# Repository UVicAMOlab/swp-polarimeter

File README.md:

## Spinning Waveplate Polarimeter

*Using a rotating quarter waveplate, a photodiode, and a few Python scripts, we can produce real-time visualization of the polarization state of incident light. This fully integrated system is easily calibrated and an affordable alternative to other fussy optical technologies making it ideal for research laboratories and educational environments.*

# Real-time Detection of Polarization of Incident Light

Initially, we use the API provided by the DAQ hat to acquire a fixed number of samples for processing; typically, this is 1000 samples at 20 ksps when the waveplate is spinning between 4500 to 5500 RPM. The raw data input is then divided into segments. Each segment is numerically integrated to determine the Fourier coefficients, and furthermore, the Stokes parameters and polarization state. To minimize any statistical errors, the mean result over several segments is considered and the display is refreshed at a rate of 4 Hz.

The reconstruction of the Stokes vector is achieved by calculating the incident intensity upon the rotating waveplate as a function of the rotation angle when aligned horizontally. We assume that the waveplate has some arbitrary retardance instead of considering a precisely calibrated quarter waveplate. Lastly, using the orthogonality of trigonometric functions we can extract the Stokes parameters S<sub>0</sub>, S<sub>1</sub>, S<sub>2</sub> and S<sub>3</sub>. Using the Stokes parameters, the degree of polarization of the incident light is also obtained through a trivial calculation.

Please see our more rigorous [explanation]#(REPLACE WITH PAPER LOCATION) and [analysis](https://github.com/UVicAMOlab/swp-polarimeter/blob/main/resources-and-documentation/analysis/Polarimeter_Analysis.pdf) for more details.

# Information Obtained from Polarimeter

The continuous data input through the Raspberry Pi's MCC DAQ hat along with the included software allows for the real-time determination and visualization of several polarization parameters. These include:

- Polarization ellipse/type of polarization (2D or 3D available)
- Stokes parameters as bar graph
- Poincaré sphere
- Degree of polarization
- Mean input signal over several segments of data
- Waveform incident on photodiode

# Getting Started

**PHYSICAL APPARATUS:**

Our spinning waveplate polarimeter utilizes a high-speed motor connected to an internally threaded rotating lens tube by a timing belt. Low friction ball bearings press-fit into the main base housing the lens tube. A polymer zero-order waveplate is threaded inside the tube. At the top of the timing belt, the upper gear contains a small magnet that is detected by the hall sensor which provides a reference angle and acquisition triggering. We chose a photodiode with an integrated transimpedance of 100 $k\Omega$ followed by a second non-inverting opamp with a variable gain from 1 to 11 via an accessible 10 $k\Omega$ potentiometer. The photodetection circuitry is housed by a 3D printed adapter plate which contains a thick polarizing sheet. The photodiode and hall sensor trigger outputs are sent into the Raspberry Pi computer which is modified with a 12 bit, 100 ksps data acquisition hat (DAQ).

All mechanical designs are open source and can be found in the [CAD-parts-2024 folder](https://github.com/UVicAMOlab/swp-polarimeter/blob/main/CAD-parts-2024).

**PCB:**

All PCB designs are open source. Designs and supplemental documentation can be found in the [circuit-pcb-2024 folder](https://github.com/UVicAMOlab/swp-polarimeter/blob/main/circuit-pcb-2024).

**CODE INSTALLATION:**

For code installation simply download the .zip file or clone the repository. All necessary code is provided in the [code folder](https://github.com/UVicAMOlab/swp-polarimeter/blob/main/code). Before operation, the [daqhats folder](https://github.com/mccdaq/daqhats/tree/master/daqhats) for operating the MCC 118 DAQ HAT must be downloaded and placed in the code folder.

## Operation Instructions

Once the apparatus has been assembled and the code is available through a computer with data acquisition it is time to begin aligning the laser beam onto the photodiode ensuring it is collimated and securely fastened. 

Please see our [calibration guide](https://github.com/UVicAMOlab/swp-polarimeter/tree/main/resources-and-documentation/calibration/SWP_Calibration_Guide.pdf) for detailed instructions on device calibration.

To access the user interface, ensure the laser is on and the polarimeter is running at your desired settings. Run the file "polvis.py" to view the real time visualization of the optical state of the incident light. Warnings printed by "polvis.py" will assist in troubleshooting by diagnosing issues and suggesting remedies.

# Known Limitations

**Non-Ideal Quarter Waveplate:**

Due to the dispersive and birefringent effects of light on the waveplate it is possible that the phase shift between the fast and slow axes may deviate from the quarter waveplate condition of $\delta=\pi/2$. This can lead to an incorrect reconstruction of the polarization state. Although calibration corrects for this wavelength-dependent phase retardance, small variation in the retardance may occur over several days while lasing at a fixed wavelength. Moreover, large variation is seen with changes to the incident wavelength. For this reason, waveplate phase retardance calibration should be performed before each session using the polarimeter.

**DC Offset:**

The issue of DC offset from background lighting and dark current is also present. Although our design does not fully correct for dark current, background light is zeroed allowing a vast reduction in total DC offset. Re-calibration for background lighting is at the discretion of the user once the apparatus is stationary in a lab setting.

**Non-Constant Rotation of Quarter Waveplate:**

In practice, the rotation of the quarter waveplate is non-constant. The polarimeter angle however must be known at all points along the trace so the sine and cosine quadratures can be determined. This is accomplished by inferring the angle through linear interpolation between triggers. Residual error arises when the angular velocity is non-constant making linear interpolation inaccurate. We have found that if the quarter waveplate rotates at a high RPM the system can be assumed intrinsically inertially stable meaning changes to angular speed will be gradual over several periods. For this reason, a powerful motor is a key design component.

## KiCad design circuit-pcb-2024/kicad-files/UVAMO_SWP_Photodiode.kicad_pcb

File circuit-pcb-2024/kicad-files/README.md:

This directory contains KiCad project files. Open the .kicad_pro file to open the entire project at once.

Refer to SWPPhotodiodeGuide.pdf and ../README.md for more info.

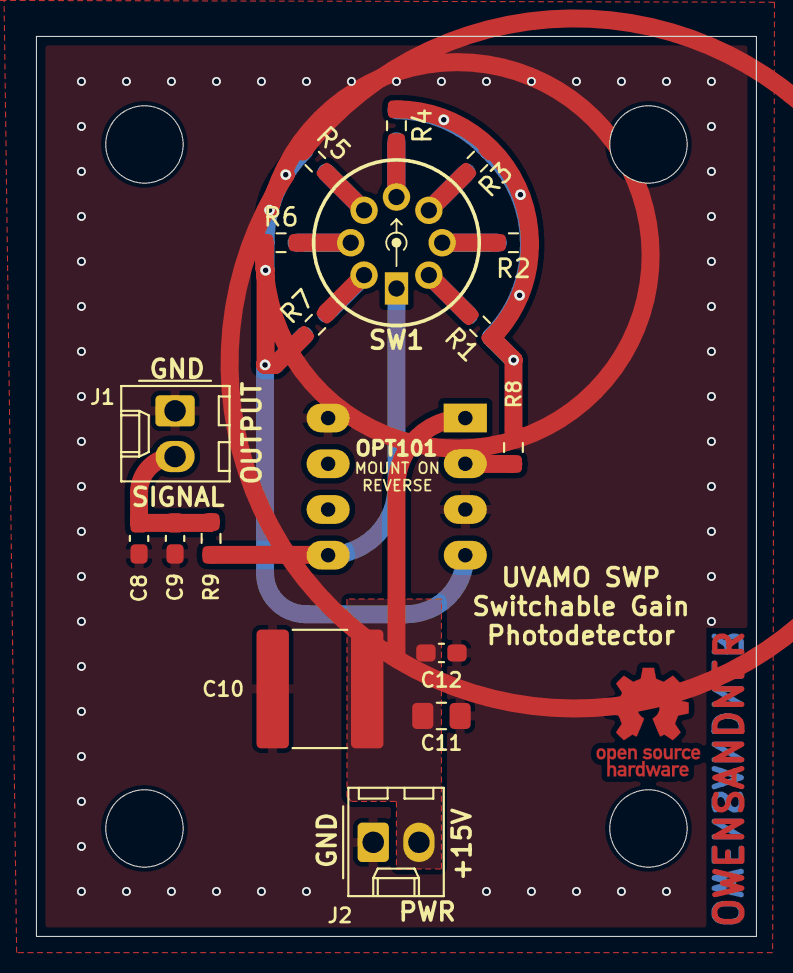
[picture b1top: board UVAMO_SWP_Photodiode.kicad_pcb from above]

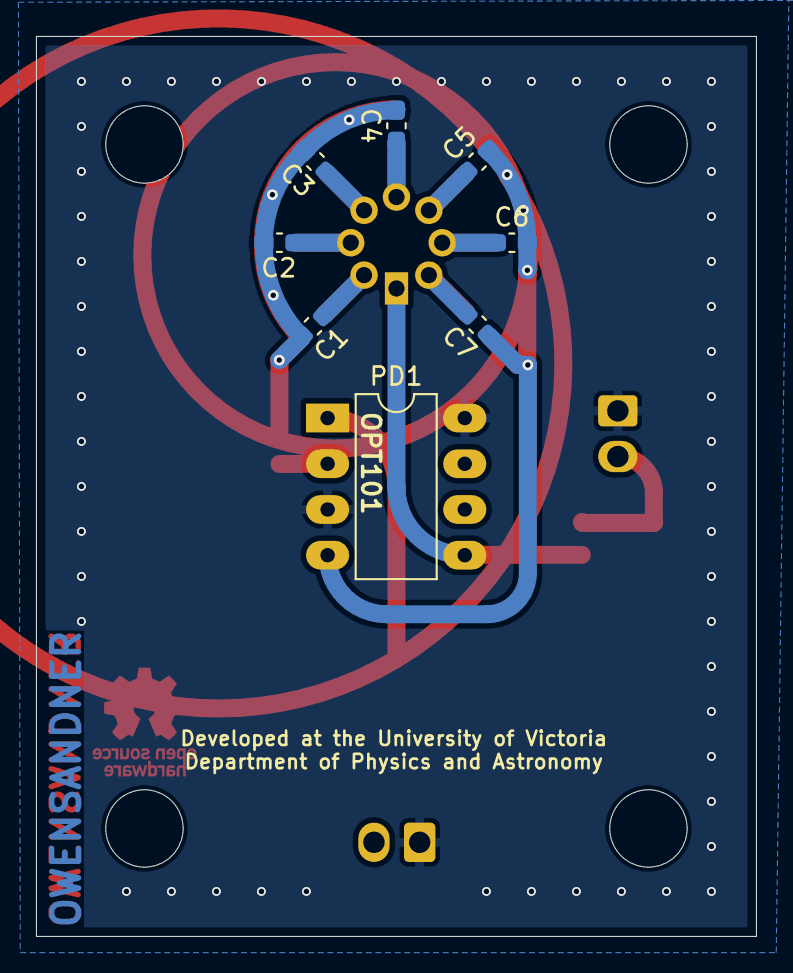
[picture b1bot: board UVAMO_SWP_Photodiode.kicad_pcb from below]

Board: 2 copper layers, 40.0 x 50.0 mm, 29 parts (8 on the bottom side), 13 nets.

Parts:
C1: 82pF; C_0603_1608Metric_Pad1.08x0.95mm_HandSolder
C2, C3: 56pF; C_0603_1608Metric_Pad1.08x0.95mm_HandSolder
C4: 39pF; C_0603_1608Metric_Pad1.08x0.95mm_HandSolder
C5: 51pF; C_0603_1608Metric_Pad1.08x0.95mm_HandSolder
C6: 2.5pF; C_0603_1608Metric_Pad1.08x0.95mm_HandSolder
C7: 0pF; C_0603_1608Metric_Pad1.08x0.95mm_HandSolder
C8, C9: 100pF; C_0603_1608Metric_Pad1.08x0.95mm_HandSolder
C10: 1uF; C_2225_5664Metric_Pad1.80x6.60mm_HandSolder
C11: 100nF; C_0805_2012Metric_Pad1.18x1.45mm_HandSolder
C12: 10nF; C_0603_1608Metric_Pad1.08x0.95mm_HandSolder
H1, H2, H3, H4: MountingHole; MountingHole_4.3mm_M4
J1, J2: Conn_01x02_Pin; Molex_KK-254_AE-6410-02A_1x02_P2.54mm_Vertical
PD1: DIP-8_W7.62mm_LongPads
R1: 3.3k; R_0603_1608Metric_Pad0.98x0.95mm_HandSolder
R2: 22k; R_0603_1608Metric_Pad0.98x0.95mm_HandSolder
R3: 43k; R_0603_1608Metric_Pad0.98x0.95mm_HandSolder
R4: 220k; R_0603_1608Metric_Pad0.98x0.95mm_HandSolder
R5: 1M; R_0603_1608Metric_Pad0.98x0.95mm_HandSolder
R6: 20M; R_0603_1608Metric_Pad0.98x0.95mm_HandSolder
R7: 50M; R_0603_1608Metric_Pad0.98x0.95mm_HandSolder
R8: 1k; R_0603_1608Metric_Pad0.98x0.95mm_HandSolder
R9: 53k; R_0603_1608Metric_Pad0.98x0.95mm_HandSolder
SW1: SW_Rotary_1x7_MP; RM107-RotarySwitch

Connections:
GND: C8.2, C9.2, C10.2, C11.2, C12.2, J1.1, J2.1, PD1.3 (GND), PD1.8 (COM)
unnamed: C1.1, R1.2, SW1.7
unnamed: C1.2, C2.2, C3.2, C4.2, R1.1, R2.1, R3.1, R4.1, R8.1
unnamed: C2.1, R2.2, SW1.6
unnamed: C3.1, R3.2, SW1.5
unnamed: C4.1, C5.1, R4.2, R5.2, SW1.3, SW1.4
unnamed: C6.1, R6.2, SW1.2
unnamed: C7.2, R7.2, SW1.1
unnamed: C8.1, C9.1, J1.2, R9.2
unnamed: C5.2, C6.2, C7.1, PD1.4 (FB), R5.1, R6.1, R7.1
unnamed: PD1.2 (In-), R8.2
unnamed: PD1.5 (Out), R9.1, SW1.8
VCC: C10.1, C11.1, C12.1, J2.2, PD1.1 (V+)

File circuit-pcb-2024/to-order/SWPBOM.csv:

"Reference","Value","Datasheet","Footprint","Qty","DNP","DigiKey Part Number"
"C7","0pF","~","Capacitor_SMD:C_0603_1608Metric_Pad1.08x0.95mm_HandSolder","1","",""
"C6","2.5pF","~","Capacitor_SMD:C_0603_1608Metric_Pad1.08x0.95mm_HandSolder","1","","13-CC0603BRNPO9BN2R5CT-ND"
"R6","20M","~","Resistor_SMD:R_0603_1608Metric_Pad0.98x0.95mm_HandSolder","1","","13-RC0603JR-0720MLCT-ND"
"PD1","~","","Package_DIP:DIP-8_W7.62mm_LongPads","1","","296-23090-5-ND"
"R8","1k","~","Resistor_SMD:R_0603_1608Metric_Pad0.98x0.95mm_HandSolder","1","","311-1.00KHRCT-ND"
"R1","3.3k","~","Resistor_SMD:R_0603_1608Metric_Pad0.98x0.95mm_HandSolder","1","","311-3.30KHRCT-ND"
"R2","22k","~","Resistor_SMD:R_0603_1608Metric_Pad0.98x0.95mm_HandSolder","1","","311-22KGRCT-ND"
"R3","43k","~","Resistor_SMD:R_0603_1608Metric_Pad0.98x0.95mm_HandSolder","1","","311-43.0KHRCT-ND"
"R9","53k","~","Resistor_SMD:R_0603_1608Metric_Pad0.98x0.95mm_HandSolder","1","","311-53.6KHRCT-ND"
"R4","220k","~","Resistor_SMD:R_0603_1608Metric_Pad0.98x0.95mm_HandSolder","1","","311-220KGRCT-ND"
"R5","1M","~","Resistor_SMD:R_0603_1608Metric_Pad0.98x0.95mm_HandSolder","1","","311-1.00MHRCT-ND"
"C8,C9","100pF","~","Capacitor_SMD:C_0603_1608Metric_Pad1.08x0.95mm_HandSolder","2","","311-1069-1-ND"
"C11","100nF","~","Capacitor_SMD:C_0805_2012Metric_Pad1.18x1.45mm_HandSolder","1","","311-1140-1-ND"
"C10","1uF","~","Capacitor_SMD:C_2225_5664Metric_Pad1.80x6.60mm_HandSolder","1","","445-2304-1-ND"
"C5","51pF","~","Capacitor_SMD:C_0603_1608Metric_Pad1.08x0.95mm_HandSolder","1","","478-10326-1-ND"
"C4","39pF","~","Capacitor_SMD:C_0603_1608Metric_Pad1.08x0.95mm_HandSolder","1","","478-KGM15ACG1H390JTCT-ND"
"C2,C3","56pF","~","Capacitor_SMD:C_0603_1608Metric_Pad1.08x0.95mm_HandSolder","2","","478-KGM15ACG1H560JTCT-ND"
"C1","82pF","~","Capacitor_SMD:C_0603_1608Metric_Pad1.08x0.95mm_HandSolder","1","","478-KGM15ACG1H820JTCT-ND"
"C12","10nF","~","Capacitor_SMD:C_0603_1608Metric_Pad1.08x0.95mm_HandSolder","1","","490-4781-1-ND"
"R7","50M","~","Resistor_SMD:R_0603_1608Metric_Pad0.98x0.95mm_HandSolder","1","","541-47MAHCT-ND"
"J1,J2","Conn_01x02_Pin","~","Connector_Molex:Molex_KK-254_AE-6410-02A_1x02_P2.54mm_Vertical","2","","900-0022232021-ND"
"SW1","SW_Rotary_1x7_MP","~","UVAMOFootprints:RM107-RotarySwitch","1","","CKN10705-ND"

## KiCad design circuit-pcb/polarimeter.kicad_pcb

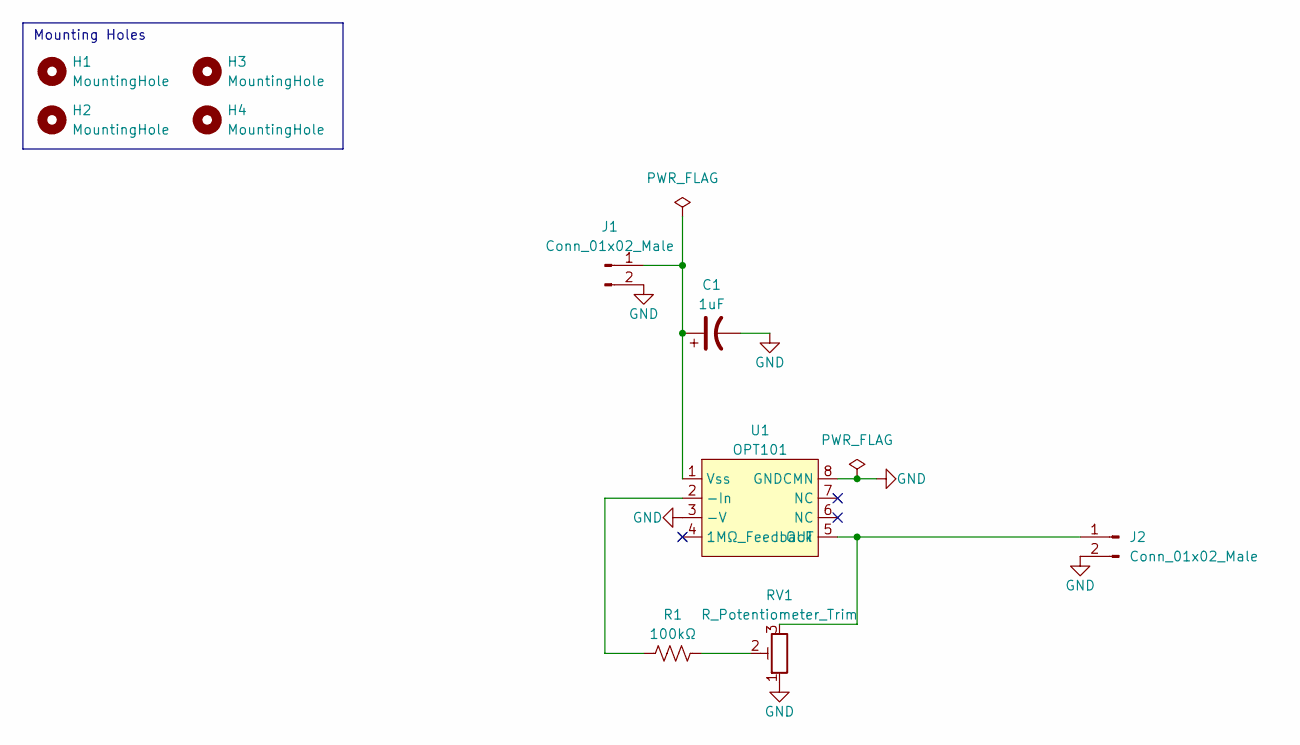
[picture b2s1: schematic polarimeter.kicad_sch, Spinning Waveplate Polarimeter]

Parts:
C1: 1uF; CP_Radial_D6.3mm_P2.50mm
H1, H2, H3, H4: MountingHole; MountingHole_4.3mm_M4
J1, J2: Conn_01x02_Male; PinHeader_1x02_P2.54mm_Vertical
R1: 100kΩ; R_Axial_DIN0207_L6.3mm_D2.5mm_P10.16mm_Horizontal
RV1: R_Potentiometer_Trim; Potentiometer_ACP_CA9-H2,5_Horizontal
U1: OPT101; DIP-8_W7.62mm

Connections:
GND: C1.2, J1.2, J2.2, RV1.1, U1.3 (-V), U1.8 (GNDCMN)
unnamed: C1.1, J1.1, U1.1 (Vss)
unnamed: J2.1, RV1.3, U1.5 (OUT)
unnamed: R1.1, U1.2 (-In)
unnamed: R1.2, RV1.2

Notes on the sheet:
Mounting Holes

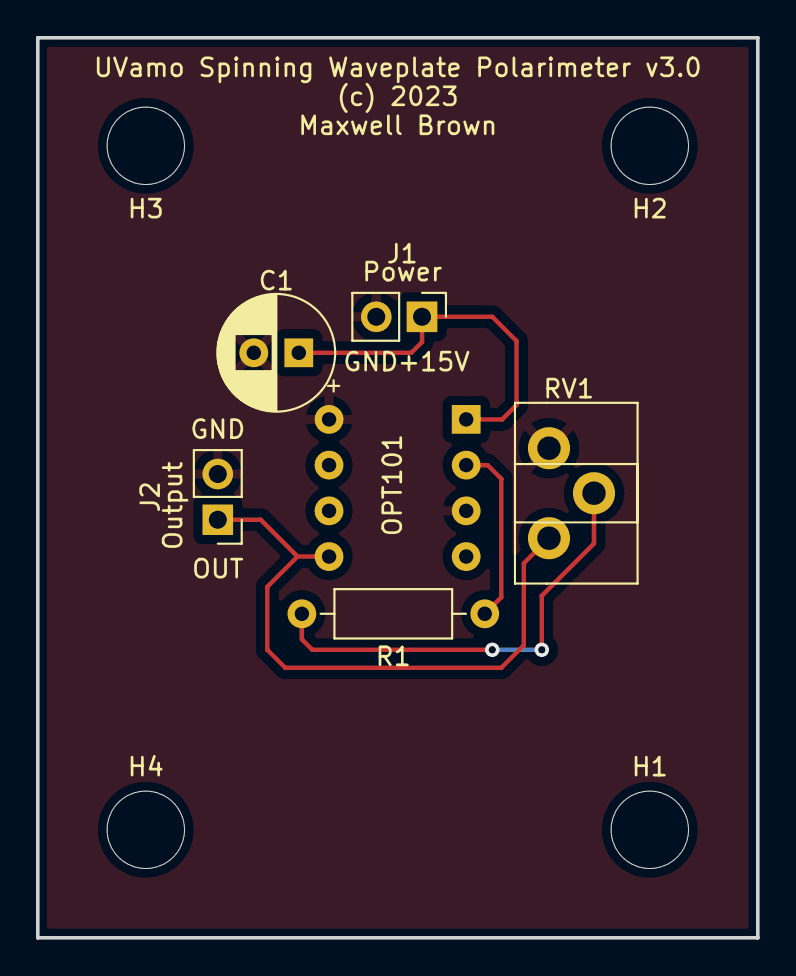
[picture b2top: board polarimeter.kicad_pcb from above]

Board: 2 copper layers, 40.0 x 50.0 mm, 10 parts (1 on the bottom side), 5 nets.

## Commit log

2023-03-01 Initial commit containing all code written by previous contributers. Contains backups from before I joined the project on Jan 18th as well.
2023-03-01 Clearing up for the day.
2023-03-04 Trying to set up connection to home computer test.
2023-03-04 Minor variable name changes.
2023-03-07 Late night cleaning. Slightly improved code segmentation as well as function/variable naming to align closer to Pythons style guide, though there will still be several disagreements.
2023-03-07 Updated function calls corresponding to function name changes within swptools.py
2023-03-07 Removing legacy files and backups to clean up repository.
2023-03-07 More file removal for repository cleaning.
2023-03-15 Created fetch_input_data() helper function to help clean up our large animate_fun() function. Additionally, corrected some naming conventions.
2023-03-17 More renaming of variables. Removed some legacy comments and added a TODO regarding auto_scale_y_trace.
2023-03-22 Removed legacy scripts (snag_stokes.py snag_trace.py and ps_polvis.py). ps_polvis.py is essentailly the same as our main polvis.py except it outputs a 3d representation of the polarization of the lig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
2023-03-26 Removed legacy development script mmc_getchunk.py
2023-03-26 Improved variable naming, comments, and code segmentation. Removed legacy comments as well.
2023-03-27 Removed redundant legacy warning (already present in swptools.py), improved variable naming, removed old comments.
2023-03-27 Improved variable naming and code readability. Hopefully didnt break anything, will need to test in lab to confirm.
2023-03-27 Removed run_cal_waveplaye.py as its functionality is entirely present and better implemented in set_wave_plate.py which saves the calculated waveplate retardance into the swp settings file automatica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
2023-03-30 Created directory for pcb circuit and added kicad files.
2023-03-30 Added analysis document explaining the math behind the magic. Still seems like magic to me.
2023-03-31 Adding automatically created backup.
2023-04-02 Added analysis folder for pdf and tex files to live. Left a legacy copy of polarimeter_analysis.pdf in the main directory as I made some small corrections to spelling and format in the /analysis vers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
2023-04-02 Created rough layout for README to follow, still a few sections to be added to the outline. Will probably be incomplete until the publication of the project, will update over time.
2023-04-03 Removed redundant swpsettings file backups.
2023-04-09 Improved docstring and commenting for get_stokes_from_chunk().
2023-04-09 Created docs folder to improve project organization--all future documentation will reside within this file in subfiles.
2023-04-24 Cleanup remaining changes before leaving for two months to go work. Good luck to whomever takes over, hopefully well have a chance to collaborate soon! Please feel free to get in touch if you have an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
2023-07-18 Cleaning raspberry pi for ease of use. All future pushes should be conducted from personal computers--the raspeberry pi will only be updated with frequent pulls.
2023-07-18 TESTING COMMIT/NOTHING PRODUCTIVE DONE
2023-07-18 clear Revert "TESTING COMMIT/NOTHING PRODUCTIVE DONE" This reverts commit 4cf0473452def6454d4aef951fee81f9f5822323.
    :qw
    git config --global --edit
2023-08-01 cleanup prepping for fork merge.
2023-08-02 polvis documentation and relating changes
2023-08-02 Polvis documentation, etc (#1)
    * TESTING COMMIT/NOTHING PRODUCTIVE DONE
    * clear
    Revert "TESTING COMMIT/NOTHING PRODUCTIVE DONE"
    This reverts commit 4cf0473452def6454d4aef951fee81f9f5822323.
    :qw
    git config --global --edit
2023-08-14 readme intro
2023-08-14 readme (#2)
    * readme intro
2023-08-14 renamed diagram
2023-08-14 Diagram
    Uploading diagram from paper
2023-08-16 Diagram
2023-08-16 Readme further work
2023-08-21 adding intructs to readme
2023-08-21 Finished Readme
2023-08-21 Readme Complete (#3)
    * Finished Readme
2024-07-15 removed old pcb, exraneous files
2024-07-15 Create new PCB directory as well as README.md
    Wrote up a short README, will add PCB files and a guide for the PCB
2024-07-15 Update README.md
    Switched some file names
2024-07-15 Create Kicad file directory
2024-07-15 Added KiCad files
2024-07-15 Added order files
2024-07-16 Fixed bug in background subtraction.
2024-07-16 Added SWP Guide
2024-07-17 Create file
2024-07-18 Updated PCB Files
    Found issue in old PCB. Updated all related files
2024-07-18 Updated comments in calibrate_trigger_delay.py
    Added missing comments, adjusted one variable name to be identifiable.
2024-07-18 Updating comments to set_waveplate.py
    Added comment descriptions to code.
2024-07-19 Delete circuit-pcb-2024/SWPPhotodiodeGuide.pdf
    Uploading new guide for updated circuit
2024-07-19 Update README.md
    Literally just changed a word
2024-07-19 name changes and git ingmore
    added settings to git_ignore
    changed simulation variable names to be consistent with online names
2024-07-19 Update README.md
    Added some pricing info
2024-07-19 Added Calibrate Background
2024-07-19 First draft at automatic selection of v_max and v_min for wave_cal
2024-07-19 Testing
2024-07-19 Update with main
2024-07-19 Updated set_waveplate
2024-07-19 Added Filtering
2024-07-22 Added Motor Jitter Estimation
2024-07-22 Fixed issue?
2024-07-23 Updated Filters
2024-07-24 Added some CAD files, added data logging functionality, and created test script for brewster experiment
2024-07-29 Organization and last touches on existing code
2024-07-30 Initial Commit. Basic framework. Not functional.
2024-07-30 Implemented Poincare sphere
    ToDo: history of last N points
2024-07-30 move ps_polvis
2024-07-30 fixed bug in gen_default_json.py
    Now creates directory if doesn't exist
2024-07-30 Updates and remerged from main
2024-07-30 update_datasheets
2024-08-02 Clean_up_final

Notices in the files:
circuit-pcb/polarimeter.kicad_pcb:
(c) 2023
